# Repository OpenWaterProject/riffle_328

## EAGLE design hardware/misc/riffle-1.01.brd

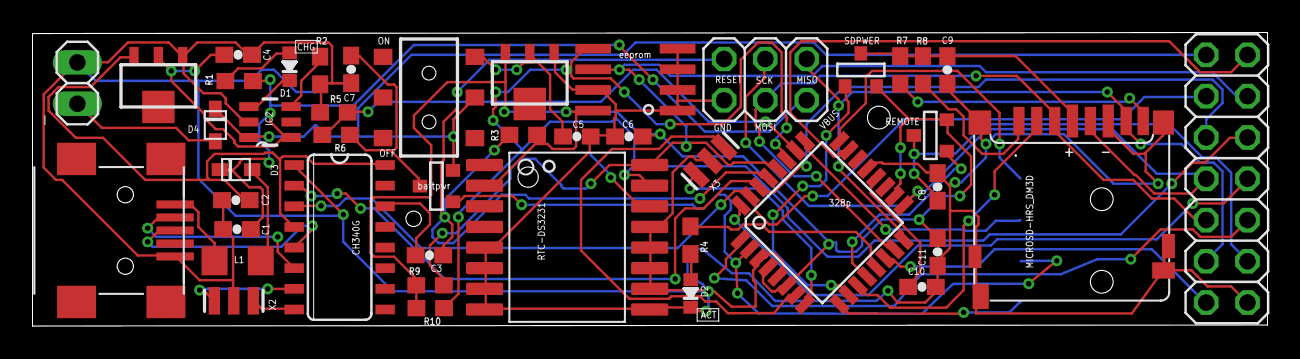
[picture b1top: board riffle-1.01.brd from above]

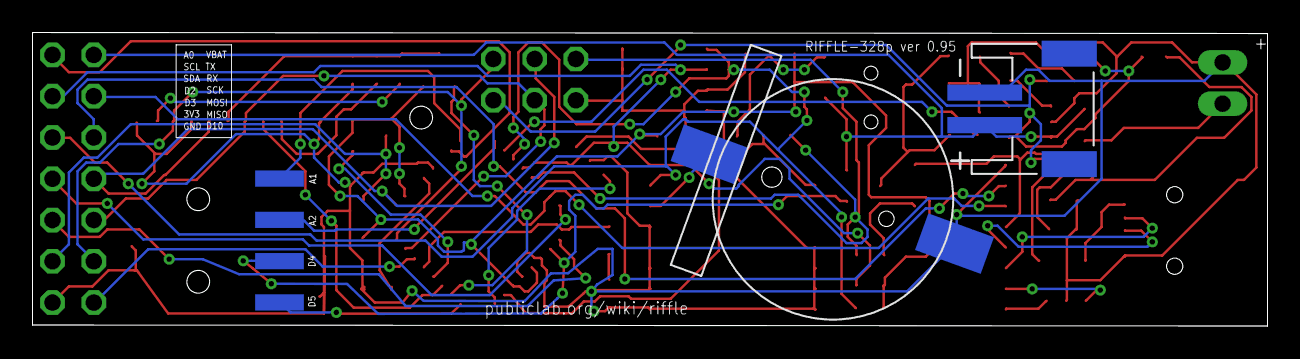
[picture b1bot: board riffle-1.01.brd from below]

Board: 2 copper layers, 76.0 x 18.1 mm, 47 parts (3 on the bottom side), 48 nets.

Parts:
BAT: CR1220; BATTCON_12MM_SMT
BATTPOWER: FDN340P; SOT-23
C1, C4, C5, C6: 10uF; 0603-CAP
C2, C3, C7, C8, C9, C10, C11: 0.1uF; 0603-CAP
CN1: JST-PH-2-SMT-RA
CN2: USB-MINIB
D1, D2: LED0603; 0603-LED
D3, D4: SOD-323F
IC1: ATMEGA328P; TQFP32-08
IC2: MCP73831; SOT23-5
IC3: CH340G; SO16
IC4, IC6: MCP1700-33; SOT89
IC5: 24AA128SN; SO-08
ISP: 2X03
J1: AYZ0202
JP1: 1X02
JP3: 1X04-SMD
JP5: 2X07
L1: 500mA; R1206
R1, R3, R4, R5, R6, R9, R10: 10K; 0603-NO
R2: 4.7K; 0603-NO
R7, R8: 50K; 0603-NO
REMOTE: FDN340P; SOT-23
RTC-DS3231: DS3231
SDPWER: FDN340P; SOT-23
U$1: MICROSD-HRS_DM3D; DM3D
X2: 12MHz; RESONATOR-SMD
X3: 16 MHz; RESONATOR-SMD

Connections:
A0: IC1.23, JP5.13
A1: IC1.24, JP3.1
A2: IC1.25, JP3.2
A3: IC1.26, R5.2, R6.1
AREF: C10.1, IC1.20
D2: IC1.32, JP5.7
D3: IC1.1, JP5.5
D4: BATTPOWER.3, IC1.2, JP3.3
D5: IC1.9, JP3.4
D6: IC1.10, SDPWER.3
D7: IC1.11, U$1.CD/DAT3
D8: IC1.12, REMOTE.3
D9: IC1.13, R4.2
D10: IC1.14, JP5.2
D+: CN2.D+, IC3.5
D-: CN2.D-, IC3.6
GND: BAT.P$1, C1.1, C2.2, C4.2, C5.2, C6.2, C7.1, C8.2, C9.1, C10.2, C11.1, CN1.2, CN2.GND, D2.MINUS, IC1.3, IC1.5, IC1.21, IC2.2, IC3.1, IC4.1, IC5.1, IC5.2, IC5.3, IC5.4, IC5.7, IC6.1, ISP.6, JP1.1, JP5.1, R2.1, R5.1, RTC-DS3231.5, RTC-DS3231.6, RTC-DS3231.7, RTC-DS3231.8, RTC-DS3231.9, RTC-DS3231.10, RTC-DS3231.11, RTC-DS3231.12, RTC-DS3231.13, U$1.GND1, U$1.GND2, U$1.GND3, U$1.GND4, U$1.SW_A, U$1.SW_B, U$1.VSS, X2.2, X3.2
MISO: IC1.16, ISP.1, JP5.4, U$1.DAT0
MOSI: IC1.15, ISP.4, JP5.6, U$1.CMD
unnamed: D1.PLUS, R1.1
unnamed: IC1.7, X3.1
unnamed: IC1.8, X3.3
unnamed: C9.2, R7.1, R8.2, SDPWER.1, U$1.VDD
unnamed: D1.MINUS, IC2.1
unnamed: IC2.5, R2.2
unnamed: C8.1, JP5.3, REMOTE.1
unnamed: C2.1, IC3.4, IC3.16, IC6.3
unnamed: D3.A, L1.2
unnamed: IC3.7, X2.1
unnamed: IC3.8, X2.3
unnamed: D4.A, JP1.2
unnamed: BATTPOWER.1, C7.2, R6.2
unnamed: R7.2, U$1.DAT1
unnamed: D2.PLUS, R4.1
unnamed: R8.1, U$1.DAT2
unnamed: CN2.VBUS, L1.1
RESET: C3.1, IC1.29, ISP.5, R3.1
RST: C3.2, IC3.14
RTC_BATT: BAT.P$2, RTC-DS3231.14
RXD: IC1.30, IC3.2, JP5.10
SCK: IC1.17, ISP.3, JP5.8, U$1.CLK
SCL: IC1.28, IC5.6, JP5.11, R9.1, RTC-DS3231.16
SDA: IC1.27, IC5.5, JP5.9, R10.1, RTC-DS3231.15
TXD: IC1.31, IC3.3, JP5.12
VBAT: BATTPOWER.2, CN1.1, D4.C, IC2.3, J1.2, JP5.14
VBUS: C1.2, C4.1, D3.C, IC2.4, IC6.2, ISP.2, R1.2
VCC: C6.1, C11.2, IC1.4, IC1.6, IC1.18, IC4.3, IC5.8, R3.2, R9.2, R10.2, REMOTE.2, RTC-DS3231.2, SDPWER.2
VDD: C5.1, IC4.2, J1.1

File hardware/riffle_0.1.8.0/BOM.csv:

Part,Details,Device,Package,Description,,MF,Cost per 100,cost,Source
BAT,CR1220,BATTERYBATTERY_12MM_SMT,BATTCON_12MM_SMT,Battery Holders,,,1.8,1.8,http://www.digikey.com/product-detail/en/1056TR/1056KCT-ND/4772075
"BATTPOWER, REMOTE, SDPWER",FDN340P,PMOSSOT23,SOT-23,MOS FET,,,0.24,0.72,http://www.digikey.com/product-detail/en/FDN340P/FDN340PCT-N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
"C1,C4,C5,C6",10uF,CAP0603-CAP,0603-CAP,Capacitor,*,,0.07,0.28,http://www.digikey.com/product-detail/en/CC0603MRX5R5BB106/3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
"C2,C3,C7,C8,C9,C10,C11",0.1uF,CAP0603-CAP,0603-CAP,Capacitor,*,,0.04,0.28,http://www.digikey.com/product-detail/en/C0603C104J4RACTU/39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
CN1,,JST_2PIN-SMT-RA,JST-PH-2-SMT-RA,JST 2-Pin Connectors of various flavors,,,0.4,0.4,http://www.digikey.com/product-detail/en/S2B-PH-SM4-TB%28LF%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
D1,LED0603,LED0603,0603-LED,,*,blue,0.23,0.23,http://www.digikey.com/product-detail/en/APT1608QBC%2FD/754-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
D2,LED0603,LED0603,0603-LED,,,yellow,0.17,0.17,http://www.digikey.com/product-detail/en/APT1608SYCK/754-112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
"D3, D4",SCHOTTKY,DIODE_SOD-123FL,SOD-123FL,Diode,,,0.22,0.44,http://www.digikey.com/product-detail/en/SM4002PL-TP/SM4002P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
IC1,ATMEGA328P,MEGA8-AI,TQFP32-08,MICROCONTROLLER,*,ATMEGA8-16AU,2.7,2.7,http://www.digikey.com/product-detail/en/ATMEGA328P-AU/ATMEG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
IC2,MCP73831,MCP73831,SOT23-5,Microchip's MCP73831,,,0.42,0.42,http://www.digikey.com/product-detail/en/MCP73831T-2ACI%2FOT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
IC3,CH340G,CH340G,SO16,,,,0.6,0.6,rui
"IC4, IC6",MCP1700-33,MCP1700SOT89,SOT89,VOLTAGE REGULATOR,*,,0.29,0.58,http://www.digikey.com/product-detail/en/0/MCP1700T3302EMBCT-ND
IC5,24AA128SN,24AA128SN,SO-08,Serial EEPROM,,24AA128-I/SN,0.5,0.5,http://www.digikey.com/product-detail/en/24AA128-I%2FSN/24AA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
ISP,,PINHD-2X3,2X03,PIN HEADER,,,,,(leave open for programming)
J1,AYZ0202,AYZ0202,AYZ0202,SPDT Slide Switch,,,1.07,1.07,http://www.digikey.com/product-detail/en/AYZ0202AGRLC/401-20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
JP1,,PINHD-1X2,1X02,PIN HEADER,,,,,(leave open)
JP3,,M04SMD,1X04-SMD,Header 4,,,,,(leave open)
JP5,,PINHD-2X7,2X07,PIN HEADER,,,0.98,0.98,http://www.digikey.com/product-detail/en/PPTC072LJBN-RC/S552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
L1,500mA,PTCFUSE-1206,R1206,"PTC fuses, resettable thermistors",,,0.17,0.17,http://www.digikey.com/product-detail/en/0ZCA0050FF2G/507-14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
"R1,R3,R4,R5,R6,R9,R10",10K,RESISTOR_0603_NOOUT,0603-NO,Resistors,*,,0.02,0.14,http://www.digikey.com/product-detail/en/CR0603-JW-103GLF/CR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
R2,4.7K,RESISTOR_0603_NOOUT,0603-NO,Resistors,*,,0.11,0.11,http://www.digikey.com/product-detail/en/MCT0603MD4701DP500/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
"R7,R8",50K,RESISTOR_0603_NOOUT,0603-NO,Resistors,*,,0.005,0.01,http://www.digikey.com/product-detail/en/RC0603JR-07100RL/31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
RTC-DS3231,DS3231,DS3231,DS3231,,,,6.3,6.3,http://www.digikey.com/product-detail/en/DS3231S%23/DS3231S%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
U$1,MICROSD-HRS_DM3D,MICROSD-HRS_DM3D,DM3D,,*,,1.5,1.5,http://www.digikey.com/product-detail/en/DM3D-SF/HR1941CT-ND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
U$4,,"USB-AB""",USB-AB-MICRO-SMD_V02_BOSS,This is a USB AB connector that is compatible with USB OTG. i.e. this connector can serve as a host or device,,,0.6,0.6,http://www.digikey.com/product-detail/en/10104111-0001LF/609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
X2,12MHz,RESONATORSMD,RESONATOR-SMD,Resonator,,X,0.4,0.4,https://www.digikey.com/product-detail/en/CSTCE12M0G55-R0/49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
X3,16 MHz,RESONATORSMD,RESONATOR-SMD,Resonator,*,,0.32,0.32,http://www.digikey.com/product-detail/en/CSTCE16M0V53-R0/490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

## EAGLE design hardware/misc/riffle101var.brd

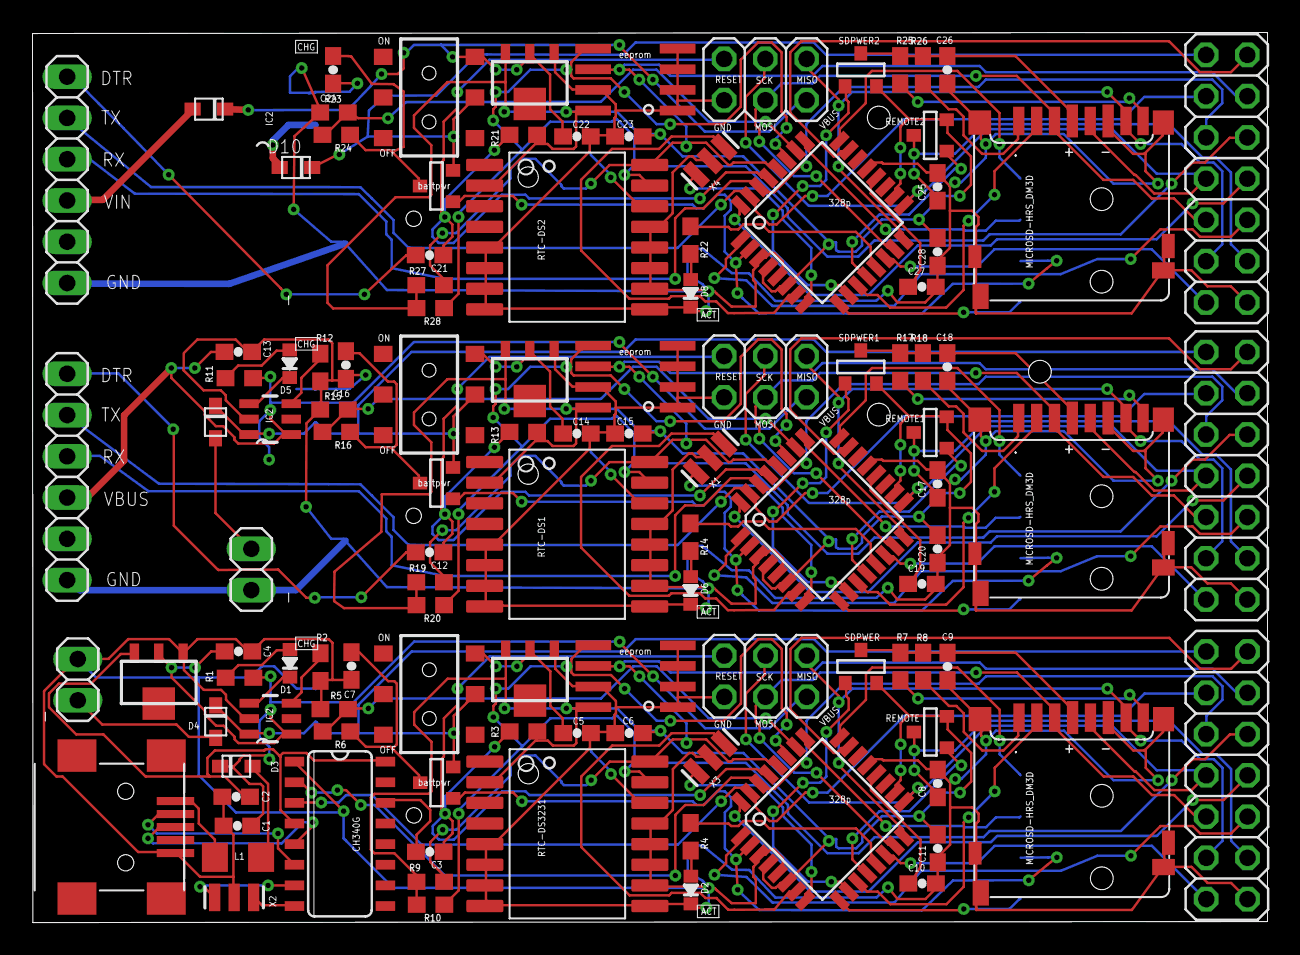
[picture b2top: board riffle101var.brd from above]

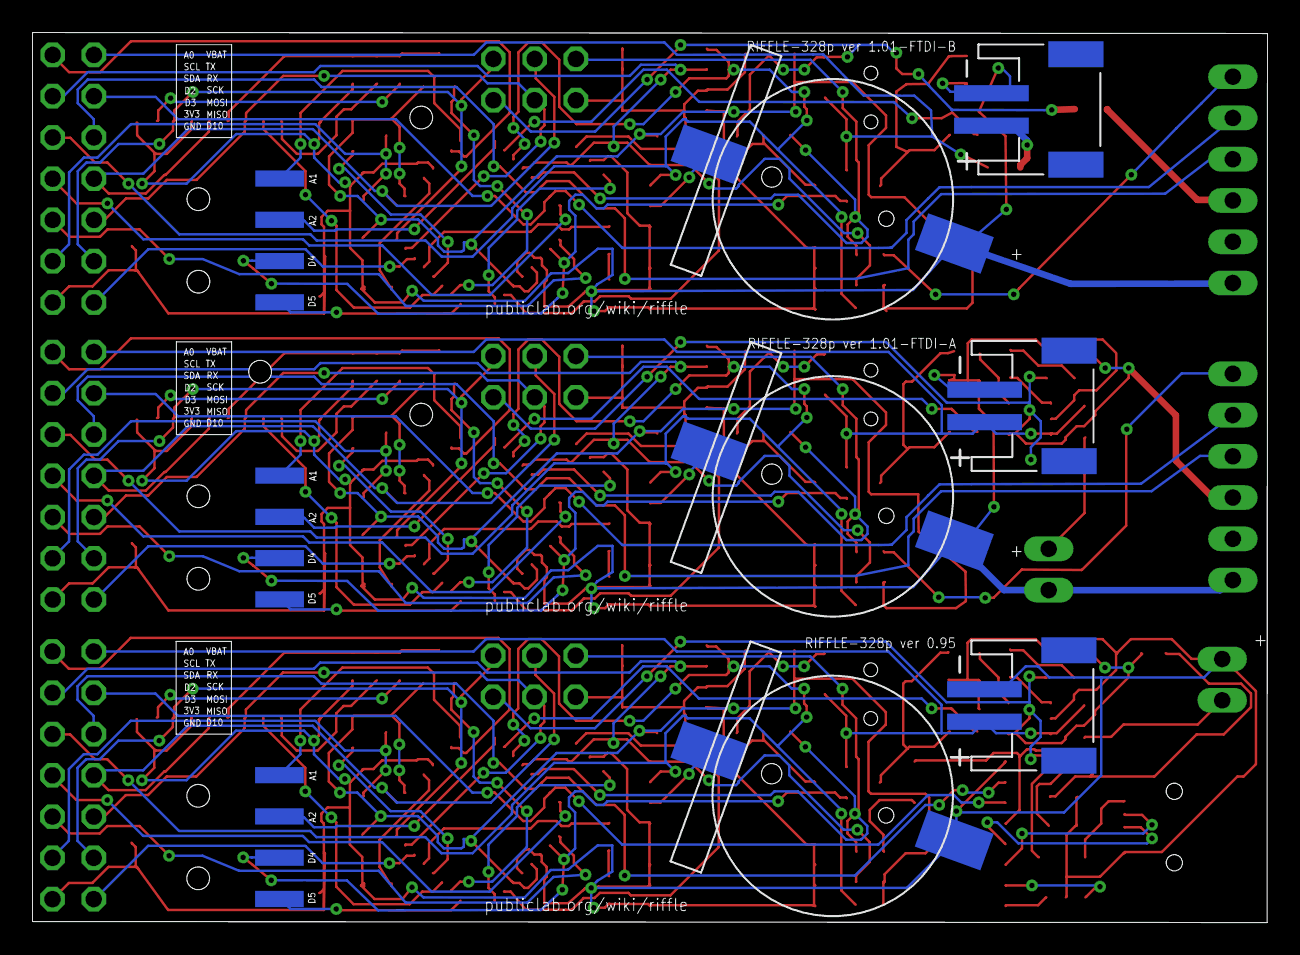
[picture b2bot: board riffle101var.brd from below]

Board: 2 copper layers, 76.0 x 54.8 mm, 122 parts (9 on the bottom side), 127 nets.

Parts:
BAT, BAT1, BAT2: CR1220; BATTCON_12MM_SMT
BATTPOWER, BATTPOWER1, BATTPOWER2: FDN340P; SOT-23
C1, C4, C5, C6, C13, C14, C15, C22, C23: 10uF; 0603-CAP
C2, C3, C7, C8, C9, C10, C11, C12, C16, C17, C18, C19, C20, C21, C24, C25, C26, C27, C28: 0.1uF; 0603-CAP
CN1, CN3, CN4: JST-PH-2-SMT-RA
CN2: USB-MINIB
D1, D2, D5, D6, D8: LED0603; 0603-LED
D3, D4, D7, D9, D10: SOD-323F
IC1, IC8, IC11: ATMEGA328P; TQFP32-08
IC2, IC7: MCP73831; SOT23-5
IC3: CH340G; SO16
IC4, IC6, IC9, IC12: MCP1700-33; SOT89
IC5, IC10, IC13: 24AA128SN; SO-08
ISP, ISP1, ISP2: 2X03
J1, J2, J3: AYZ0202
JP1, JP2: 1X02
JP3, JP4, JP8: 1X04-SMD
JP5, JP6, JP9: 2X07
JP7, JP10: 1X06
L1: 500mA; R1206
R1, R3, R4, R5, R6, R9, R10, R11, R13, R14, R15, R16, R19, R20, R21, R22, R23, R24, R27, R28: 10K; 0603-NO
R2, R12: 4.7K; 0603-NO
R7, R8, R17, R18, R25, R26: 50K; 0603-NO
REMOTE, REMOTE1, REMOTE2: FDN340P; SOT-23
RTC-DS1, RTC-DS2, RTC-DS3231: DS3231
SDPWER, SDPWER1, SDPWER2: FDN340P; SOT-23
U$1, U$2, U$3: MICROSD-HRS_DM3D; DM3D
X1, X3, X4: 16 MHz; RESONATOR-SMD
X2: 12MHz; RESONATOR-SMD

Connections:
A0: IC1.23, JP5.13
A1: IC1.24, JP3.1
A2: IC1.25, JP3.2
A3: IC1.26, R5.2, R6.1
A4: IC8.23, JP6.13
A5: IC8.25, JP4.2
A6: IC8.26, R15.2, R16.1
A7: IC8.24, JP4.1
A8: IC11.23, JP9.13
A9: IC11.25, JP8.2
A10: IC11.26, R23.2, R24.1
A11: IC11.24, JP8.1
AREF: C10.1, IC1.20
AREF1: C19.1, IC8.20
AREF2: C27.1, IC11.20
D1: IC8.13, R14.2
D2: IC1.32, JP5.7
D3: IC1.1, JP5.5
D4: BATTPOWER.3, IC1.2, JP3.3
D5: IC1.9, JP3.4
D6: IC1.10, SDPWER.3
D7: IC1.11, U$1.CD/DAT3
D8: IC1.12, REMOTE.3
D9: IC1.13, R4.2
D10: IC1.14, JP5.2
D11: BATTPOWER1.3, IC8.2, JP4.3
D12: IC8.12, REMOTE1.3
D13: IC8.1, JP6.5
D14: IC8.9, JP4.4
D15: IC8.10, SDPWER1.3
D16: IC8.11, U$2.CD/DAT3
D17: IC8.32, JP6.7
D18: IC8.14, JP6.2
D19: IC11.13, R22.2
D20: BATTPOWER2.3, IC11.2, JP8.3
D21: IC11.12, REMOTE2.3
D22: IC11.1, JP9.5
D23: IC11.9, JP8.4
D24: IC11.10, SDPWER2.3
D25: IC11.11, U$3.CD/DAT3
D26: IC11.32, JP9.7
D27: IC11.14, JP9.2
D+: CN2.D+, IC3.5
D-: CN2.D-, IC3.6
GND: BAT.P$1, C1.1, C2.2, C4.2, C5.2, C6.2, C7.1, C8.2, C9.1, C10.2, C11.1, CN1.2, CN2.GND, D2.MINUS, IC1.3, IC1.5, IC1.21, IC2.2, IC3.1, IC4.1, IC5.1, IC5.2, IC5.3, IC5.4, IC5.7, IC6.1, ISP.6, JP1.1, JP5.1, R2.1, R5.1, RTC-DS3231.5, RTC-DS3231.6, RTC-DS3231.7, RTC-DS3231.8, RTC-DS3231.9, RTC-DS3231.10, RTC-DS3231.11, RTC-DS3231.12, RTC-DS3231.13, U$1.GND1, U$1.GND2, U$1.GND3, U$1.GND4, U$1.SW_A, U$1.SW_B, U$1.VSS, X2.2, X3.2
GND1: BAT1.P$1, C13.2, C14.2, C15.2, C16.1, C17.2, C18.1, C19.2, C20.1, CN3.2, D6.MINUS, IC7.2, IC8.3, IC8.5, IC8.21, IC9.1, IC10.1, IC10.2, IC10.3, IC10.4, IC10.7, ISP1.6, JP2.1, JP6.1, JP7.1, R12.1, R15.1, RTC-DS1.5, RTC-DS1.6, RTC-DS1.7, RTC-DS1.8, RTC-DS1.9, RTC-DS1.10, RTC-DS1.11, RTC-DS1.12, RTC-DS1.13, U$2.GND1, U$2.GND2, U$2.GND3, U$2.GND4, U$2.SW_A, U$2.SW_B, U$2.VSS, X1.2
GND2: BAT2.P$1, C22.2, C23.2, C24.1, C25.2, C26.1, C27.2, C28.1, CN4.2, D8.MINUS, IC11.3, IC11.5, IC11.21, IC12.1, IC13.1, IC13.2, IC13.3, IC13.4, IC13.7, ISP2.6, JP9.1, JP10.1, R23.1, RTC-DS2.5, RTC-DS2.6, RTC-DS2.7, RTC-DS2.8, RTC-DS2.9, RTC-DS2.10, RTC-DS2.11, RTC-DS2.12, RTC-DS2.13, U$3.GND1, U$3.GND2, U$3.GND3, U$3.GND4, U$3.SW_A, U$3.SW_B, U$3.VSS, X4.2
MISO: IC1.16, ISP.1, JP5.4, U$1.DAT0
MISO1: IC8.16, ISP1.1, JP6.4, U$2.DAT0
MISO2: IC11.16, ISP2.1, JP9.4, U$3.DAT0
MOSI: IC1.15, ISP.4, JP5.6, U$1.CMD
MOSI1: IC8.15, ISP1.4, JP6.6, U$2.CMD
MOSI2: IC11.15, ISP2.4, JP9.6, U$3.CMD
unnamed: D1.PLUS, R1.1
unnamed: IC1.7, X3.1
unnamed: IC1.8, X3.3
unnamed: C9.2, R7.1, R8.2, SDPWER.1, U$1.VDD
unnamed: D1.MINUS, IC2.1
unnamed: IC2.5, R2.2
unnamed: C8.1, JP5.3, REMOTE.1
unnamed: C2.1, IC3.4, IC3.16, IC6.3
unnamed: D5.MINUS, IC7.1
unnamed: D3.A, L1.2
unnamed: IC3.7, X2.1
unnamed: IC7.5, R12.2
unnamed: IC3.8, X2.3
unnamed: D4.A, JP1.2
unnamed: BATTPOWER.1, C7.2, R6.2
unnamed: R7.2, U$1.DAT1
unnamed: D2.PLUS, R4.1
unnamed: R8.1, U$1.DAT2
unnamed: CN2.VBUS, L1.1
unnamed: IC8.7, X1.1
unnamed: IC8.8, X1.3
unnamed: C17.1, JP6.3, REMOTE1.1
unnamed: BATTPOWER1.1, C16.2, R16.2
unnamed: R17.2, U$2.DAT1
unnamed: R18.1, U$2.DAT2
unnamed: C18.2, R17.1, R18.2, SDPWER1.1, U$2.VDD
unnamed: D6.PLUS, R14.1
unnamed: D7.A, JP2.2
unnamed: D5.PLUS, R11.1
unnamed: IC11.7, X4.1
unnamed: IC11.8, X4.3
unnamed: C25.1, JP9.3, REMOTE2.1
unnamed: BATTPOWER2.1, C24.2, R24.2
unnamed: R25.2, U$3.DAT1
unnamed: R26.1, U$3.DAT2
unnamed: C26.2, R25.1, R26.2, SDPWER2.1, U$3.VDD
unnamed: D8.PLUS, R22.1
unnamed: D9.A, JP10.3
unnamed: CN4.1, D10.A
RESET: C3.1, IC1.29, ISP.5, R3.1
RESET1: C12.1, IC8.29, ISP1.5, R13.1
RESET2: C21.1, IC11.29, ISP2.5, R21.1
RST: C3.2, IC3.14
RST1: C12.2, JP7.6
RST2: C21.2, JP10.6
RTC_BATT: BAT.P$2, RTC-DS3231.14
RTC_BATT1: BAT1.P$2, RTC-DS1.14
RTC_BATT2: BAT2.P$2, RTC-DS2.14
RXD: IC1.30, IC3.2, JP5.10
RXD1: IC8.30, JP6.10, JP7.4
RXD2: IC11.30, JP9.10, JP10.4
SCK: IC1.17, ISP.3, JP5.8, U$1.CLK
SCK1: IC8.17, ISP1.3, JP6.8, U$2.CLK
SCK2: IC11.17, ISP2.3, JP9.8, U$3.CLK
SCL: IC1.28, IC5.6, JP5.11, R9.1, RTC-DS3231.16
SCL1: IC8.28, IC10.6, JP6.11, R19.1, RTC-DS1.16
SCL2: IC11.28, IC13.6, JP9.11, R27.1, RTC-DS2.16
SDA: IC1.27, IC5.5, JP5.9, R10.1, RTC-DS3231.15
SDA1: IC8.27, IC10.5, JP6.9, R20.1, RTC-DS1.15
SDA2: IC11.27, IC13.5, JP9.9, R28.1, RTC-DS2.15
TXD: IC1.31, IC3.3, JP5.12
TXD1: IC8.31, JP6.12, JP7.5
TXD2: IC11.31, JP9.12, JP10.5
VBAT: BATTPOWER.2, CN1.1, D4.C, IC2.3, J1.2, JP5.14
VBAT1: BATTPOWER1.2, CN3.1, D7.C, IC7.3, J2.2, JP6.14
VBAT2: BATTPOWER2.2, D10.C, J3.2, JP9.14
VBUS: C1.2, C4.1, D3.C, IC2.4, IC6.2, ISP.2, R1.2
VBUS1: C13.1, IC7.4, ISP1.2, JP7.3, R11.2
VCC: C6.1, C11.2, IC1.4, IC1.6, IC1.18, IC4.3, IC5.8, R3.2, R9.2, R10.2, REMOTE.2, RTC-DS3231.2, SDPWER.2
VCC1: C15.1, C20.2, IC8.4, IC8.6, IC8.18, IC9.3, IC10.8, R13.2, R19.2, R20.2, REMOTE1.2, RTC-DS1.2, SDPWER1.2
VCC2: C23.1, C28.2, IC11.4, IC11.6, IC11.18, IC12.3, IC13.8, R21.2, R27.2, R28.2, REMOTE2.2, RTC-DS2.2, SDPWER2.2
VDD: C5.1, IC4.2, J1.1
VDD1: C14.1, IC9.2, J2.1
VIN: C22.1, D9.C, IC12.2, ISP2.2, J3.1

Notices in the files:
parts and their libraries:
microbuilder: This work is placed in the public domain, and may be freely used for commercial and non-commercial work with the following conditions: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
